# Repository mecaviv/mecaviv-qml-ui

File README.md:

# Mecaviv QML UI - Monorepo

Système complet de contrôle et visualisation pour sirènes musicales mécaniques, développé en Qt6/QML et Node.js.

## 🎯 Vue d'ensemble

Ce monorepo regroupe 4 applications interconnectées pour le contrôle, la visualisation et le monitoring de 7 sirènes musicales mécaniques. L'ensemble forme un système hiérarchique où chaque composant a un rôle spécifique dans la chaîne de contrôle et de monitoring.

## 🏗️ Architecture Globale

```
┌─────────────────────────────────────────────────────────────────┐
│                        SirenConsole                             │
│              Console de Contrôle (Priorité Max)                 │
│         Gestion de 7 pupitres - Port 8001 - WebSocket          │
└────────────────────────┬────────────────────────────────────────┘
                         │
                         │ WebSocket (contrôle + monitoring)
                         ▼
┌─────────────────────────────────────────────────────────────────┐
│                     SirenePupitre (×7)                          │
│         Visualiseurs Musicaux (Interface Locale)                │
│      Portée 3D + Contrôleurs - Port 8000 - WebSocket           │
└────────────────────────┬────────────────────────────────────────┘
                         │
                         │ UDP/WebSocket (données musicales)
                         ▼
┌─────────────────────────────────────────────────────────────────┐
│                        PureData                                 │
│              Hub de Routage MIDI + Communication                │
│        Reçoit : MIDI (Reaper, Sirénium) + UDP (Pupitres)       │
└────────────────────────┬────────────────────────────────────────┘
                         │
                         │ MIDI (contrôle physique)
                         ▼
┌─────────────────────────────────────────────────────────────────┐
│                   Sirènes Physiques (×7)                        │
│              Instruments Mécaniques + VST Virtuels              │
│                   UDP → sirenRouter (monitoring)                │
└─────────────────────────┬───────────────────────────────────────┘
                          │
                          │ UDP (monitoring passif)
                          ▼
┌─────────────────────────────────────────────────────────────────┐
│                       sirenRouter                               │
│            Service de Monitoring Centralisé                     │
│      REST API (8002) + WebSocket (8003) + UDP (8004)           │
└─────────────────────────────────────────────────────────────────┘
         │
         │ WebSocket (état temps réel)
         ▼
┌─────────────────────────────────────────────────────────────────┐
│                    pedalierSirenium                             │
│         Interface Pédalier 3D (8 pédales × 7 sirènes)          │
│     Port 8010 - WebSocket - Gestion Scènes + Presets          │
└─────────────────────────────────────────────────────────────────┘
```

## 📦 Projets Inclus

### 1. [SirenePupitre](./SirenePupitre/) - Visualiseur Musical 🎵

**Interface locale** pour visualiser en temps réel les données musicales d'une sirène.

**Fonctionnalités** :
- Portée musicale 3D avec clé de sol/fa
- Afficheurs LED 3D (Hz, RPM, note)
- Indicateurs de contrôleurs (volant, joystick, faders)
- Panneau admin (configuration, visibilité, couleurs)
- Mode console (contrôle à distance par SirenConsole)

**Technologies** : Qt 6, QML, Qt Quick 3D, WebAssembly  
**Port** : 8000  
**README** : [SirenePupitre/README.md](./SirenePupitre/README.md)

### 2. [SirenConsole](./SirenConsole/) - Console de Contrôle 🎛️

**Console centrale** pour gérer jusqu'à 7 instances de SirenePupitre.

**Fonctionnalités** :
- Vue d'ensemble de 7 pupitres
- Configuration centralisée (sirènes, contrôleurs, courbes)
- Assignation exclusive des sirènes (1 sirène = 1 pupitre)
- Mode "All" (configuration simultanée de tous les pupitres)
- Gestion de presets avec API REST
- Monitoring en temps réel

**Technologies** : Qt 6, QML, WebAssembly, Node.js  
**Port** : 8001  
**README** : [SirenConsole/README.md](./SirenConsole/README.md)

### 3. [pedalierSirenium](./pedalierSirenium/) - Interface Pédalier 3D 🎮

**Interface de contrôle 3D** pour 8 pédales contrôlant 7 sirènes.

**Fonctionnalités** :
- Vue 3D de 7 sirènes avec animations
- Matrice de configuration : 8 pédales × 7 sirènes × 8 contrôleurs = 448 paramètres
- Gestion de presets (sauvegarde/chargement)
- Gestion de scènes (64 scènes sur 8 pages)
- Contrôle de boucles (recording, playing, stopped, cleared)
- Monitoring MIDI temps réel avec portées musicales
- Debug panel avec 11 catégories de logs

**Technologies** : Qt 6, QML, Qt Quick 3D, WebAssembly, PureData  
**Port** : 8010  
**README** : [pedalierSirenium/README.md](./pedalierSirenium/README.md)

### 4. [sirenRouter](./sirenRouter/) - Service de Monitoring 📊

**Service de monitoring centralisé** pour observer l'état des sirènes.

**Fonctionnalités** :
- Monitoring passif des sirènes via UDP
- API REST pour consultation de l'état
- WebSocket pour notifications temps réel
- Dashboard web de monitoring
- Historique et logs des activités

**Technologies** : `SirenRouter.fsproj` (HTTP 8002). Le module Node de ce dossier est `src/api/control.js`.  
**Ports prévus** : 8002 (API REST), 8003 (WebSocket), 8004 (UDP)  
**README** : [sirenRouter/README.md](./sirenRouter/README.md)

## Serveurs .NET

La configuration CMake exécute `dotnet tool restore` et, si `dotnet paket` répond, `dotnet paket restore`. Depuis cette racine :

```bash
dotnet watch --non-interactive --project <projet>
dotnet run --project <projet>
```

| Projet | Rôle |
|---|---|
| `SirenManager/backend/fsharpwebserver` | API SSH / UDP, ports 8005 et 8006 |
| `SirenManager/webfiles` | fichiers WASM, port 8081 |
| `SirenePupitre/webfiles` | fichiers WASM, port 8000. L'API MIDI est `server.js` |
| `SirenConsole/webfiles` | fichiers WASM, port 8001. Presets, MIDI et `/ws` sont `server.js` |
| `pedalierSirenium/webfiles` | fichiers WASM, port 8010. Journaux, `/api` et le WebSocket 10000 sont `server.js` |
| `sirenRouter` | HTTP 8002 |

## 🚀 Installation Rapide

### Prérequis

- **Qt 6.10+** avec support WebAssembly
- **Node.js 18+** et npm
- **.NET SDK 10** (`dotnet watch`, `dotnet run`)
- **CMake 3.19+** (système de build multiplateforme)
- **Ninja** (générateur de build recommandé)
- **Google Chrome** (pour le développement web)

### Installation des Outils

```bash
# macOS
brew install cmake ninja node

# Linux
sudo apt-get install cmake ninja-build nodejs npm

# Windows
# Installer CMake: https://cmake.org/download/
# Installer Node.js: https://nodejs.org/
```

### Installation Qt WebAssembly

Télécharger Qt depuis [qt.io/download](https://www.qt.io/download) et installer les modules :
- Qt 6.10.0 (ou plus récent)
- Qt for WebAssembly (wasm_singlethread)

### Configuration des Chemins Qt

**⚠️ Important** : Le projet utilise des variables d'environnement pour les chemins Qt.

#### Configuration Rapide

```bash
# macOS / Linux
./scripts/setup-env.sh

# Windows (PowerShell)
.\scripts\setup-env.ps1
```

Le script détecte automatiquement votre système et configure les chemins Qt.

#### Configuration Manuelle

```bash
# macOS / Linux - Ajouter à ~/.zshrc ou ~/.bashrc
export QT_DIR="$HOME/Qt/6.10.0/macos"  # ou gcc_64 pour Linux
export QT_WASM_DIR="$HOME/Qt/6.10.0/wasm_singlethread"

# Windows - PowerShell ou Variables Système
$env:QT_DIR = "C:\Qt\6.10.0\msvc2019_64"
$env:QT_WASM_DIR = "C:\Qt\6.10.0\wasm_singlethread"
```

**📖 Guide détaillé** : Voir [CONFIG.md](./CONFIG.md) pour la configuration complète.

### Build de tous les projets

#### Méthode 1 : CMake (Recommandé - Multiplateforme)

```bash
# Cloner le dépôt
git clone https://github.com/mecaviv/mecaviv-qml-ui.git
cd mecaviv-qml-ui

# Configurer les variables Qt (voir CONFIG.md)
export QT_DIR="$HOME/Qt/6.10.0/macos"
export QT_WASM_DIR="$HOME/Qt/6.10.0/wasm_singlethread"

# Configuration
cmake --preset=default        # Desktop natif
# ou
cmake --preset=wasm          # WebAssembly

# Build (5-10 minutes)
cmake --build build --parallel
```

#### Méthode 2 : Scripts Bash (macOS/Linux uniquement)

```bash
# Build tous les projets
./scripts/build-all.sh
```

### Lancer un projet en mode développement

```bash
# SirenePupitre
./scripts/dev.sh sirenepupitre

# SirenConsole (serveur F#, par franz)
franz build qml-ui -p wasm -t console   # WebAssembly build, copied into SirenConsole/webfiles
franz run console-server                # F# server, https://localhost:8001 (franz stop console-server)

# pedalierSirenium
./scripts/dev.sh pedalier

# sirenRouter
./scripts/dev.sh router
```

## 📜 Build System

### CMake (Recommandé - Multiplateforme)

```bash
# Configuration
cmake --preset=default        # Desktop Debug
cmake --preset=release        # Desktop Release
cmake --preset=wasm          # WebAssembly

# Build
cmake --build build          # Build tout
cmake --build build --target appSirenePupitre  # Build un projet
cmake --build build --parallel  # Build parallèle

# Helper scripts
./scripts/configure.sh default   # macOS/Linux
.\scripts\configure.ps1 default    # Windows (PowerShell)
```

### Scripts Bash (Legacy - Unix uniquement)

```bash
./scripts/build-all.sh         # Build tous les projets
./scripts/build-project.sh <project>  # Build un projet spécifique
./scripts/dev.sh <project>     # Mode développement
./scripts/clean-all.sh         # Nettoyage complet
```

**Documentation complète** : 
- [docs/BUILD.md](./docs/BUILD.md) - Guide de build détaillé
- [scripts/README.md](./scripts/README.md) - Documentation des scripts

## 📡 Communication entre Applications

### Protocoles Utilisés

- **WebSocket** : Communication temps réel entre Console ↔ Pupitres ↔ PureData
- **UDP** : Données musicales (Pupitres → PureData, Sirènes → Router)
- **MIDI** : Contrôle physique des sirènes (PureData → Sirènes)
- **REST API** : Consultation de l'état (sirenRouter)

### Ports Utilisés

| Application | Protocol | Port(s) | Description |
|-------------|----------|---------|-------------|
| SirenePupitre | HTTP + WebSocket | 8000 | Interface web + communication |
| SirenConsole | HTTP + WebSocket | 8001 | Interface web + contrôle pupitres |
| sirenRouter | REST + WebSocket + UDP | 8002-8004 | API, notifications, monitoring |
| pedalierSirenium | HTTP + WebSocket | 8010 | Interface web + communication |
| PureData | WebSocket | 10000-10001 | Hub central de routage |

### Messages WebSocket

Voir la documentation détaillée : [docs/COMMUNICATION.md](./docs/COMMUNICATION.md)

## 📚 Documentation

- **[ARCHITECTURE.md](./docs/ARCHITECTURE.md)** : Architecture détaillée du système
- **[BUILD.md](./docs/BUILD.md)** : Guide de build complet et troubleshooting
- **[COMMUNICATION.md](./docs/COMMUNICATION.md)** : Protocoles de communication
- **[COMPOSESIREN_ARCHITECTURE.md](./docs/COMPOSESIREN_ARCHITECTURE.md)** : Architecture ComposeSiren et flux MIDI
- **[TODO.md](./TODO.md)** : Roadmap et tâches à venir

### Documentation par Projet

- [SirenePupitre/README.md](./SirenePupitre/README.md)
- [SirenConsole/README.md](./SirenConsole/README.md)
- [pedalierSirenium/README.md](./pedalierSirenium/README.md)
- [sirenRouter/README.md](./sirenRouter/README.md)

## 🎯 Use Cases Typiques

### Concert/Performance

1. **Démarrer sirenRouter** pour le monitoring
2. **Démarrer PureData** comme hub central
3. **Démarrer 7 instances de SirenePupitre** (une par sirène)
4. **Démarrer SirenConsole** pour le contrôle global
5. **Utiliser pedalierSirenium** pour les effets live

### Développement/Debug

1. **Démarrer un seul pupitre** : `./scripts/dev.sh sirenepupitre`
2. **Tester les communications** avec le debug panel
3. **Modifier le code QML** et recharger
4. **Consulter les logs** : `tail -f /tmp/sirenepupitre_server.log`

### Configuration des Sirènes

1. **Ouvrir SirenConsole**
2. **Onglet Configuration** → Sélectionner un pupitre
3. **Assigner les sirènes** (assignation exclusive)
4. **Configurer l'ambitus, la transposition, les contrôleurs**
5. **Sauvegarder en preset** pour réutiliser

## 🔧 Dépannage

### Port déjà utilisé

```bash
# Utiliser le script de nettoyage
./scripts/clean-all.sh

# Ou tuer manuellement
lsof -ti:8000 | xargs kill -9
```

### Build échoue

```bash
# Nettoyer et rebuilder
./scripts/clean-all.sh
./scripts/build-project.sh <project>
```

### Qt WebAssembly introuvable

Vérifier le chemin dans `scripts/build-project.sh` :
```bash
QT_CMAKE="$HOME/Qt/6.10.0/wasm_singlethread/bin/qt-cmake"
```

### Plus de dépannage

Voir [docs/BUILD.md](./docs/BUILD.md) pour le guide complet.

## 🗂️ Structure du Monorepo

```
mecaviv-qml-ui/
├── README.md                    # Ce fichier
├── TODO.md                      # Roadmap globale
├── .gitignore                   # Fichiers à ignorer
├── docs/                        # Documentation globale
│   ├── ARCHITECTURE.md
│   ├── BUILD.md
│   └── COMMUNICATION.md
├── scripts/                     # Scripts centralisés
│   ├── build-all.sh
│   ├── build-project.sh
│   ├── dev.sh
│   ├── clean-all.sh
│   └── README.md
├── SirenePupitre/              # Visualiseur musical
│   ├── README.md
│   ├── QML/
│   └── webfiles/
├── SirenConsole/               # Console de contrôle
│   ├── README.md
│   ├── QML/
│   └── webfiles/
├── pedalierSirenium/          # Interface pédalier 3D
│   ├── README.md
│   ├── QtFiles/
│   └── webfiles/
└── sirenRouter/                # Service monitoring
    ├── README.md
    └── src/
```

## 🤝 Contribution

Ce projet est développé par **Mécanique Vivante** pour le contrôle de sirènes musicales mécaniques.

### Workflow Git

```bash
# Travailler sur une branche
git checkout -b feature/ma-fonctionnalite

# Commiter les changements
git add .
git commit -m "Description de la fonctionnalité"

# Pousser vers le remote
git push origin feature/ma-fonctionnalite
```

## 📄 Licence

Ce projet est développé dans le cadre du projet Mécanique Vivante.

## 🆘 Support

Pour toute question :
1. Consulter la [documentation](./docs/)
2. Vérifier les [README des projets](#-projets-inclus)
3. Consulter le [TODO.md](./TODO.md) pour les fonctionnalités en cours

## 🔄 TODO - Restructuration Planifiée

### Dossier partagé `shared/` (En cours)

Pour éviter la duplication de code entre projets, création d'un dossier `shared/` à la racine du monorepo.

#### Structure prévue

```
mecaviv-qml-ui/
├── shared/
│   └── qml/
│       ├── common/              # Composants QML partagés
│       │   ├── DigitLED3D.qml
│       │   ├── LEDText3D.qml
│       │   ├── LEDSegment.qml
│       │   ├── Knob.qml
│       │   ├── Knob3D.qml
│       │   └── MusicUtils.qml
│       └── fonts/                # Polices musicales partagées
│           ├── MusiSync.ttf
│           └── NotoMusic-Regular.ttf
├── SirenePupitre/
│   └── QML/
│       └── utils/               # Composants spécifiques au pupitre
│           ├── meshes/          # Modèles 3D (reste local)
│           ├── Clef3D.qml
│           ├── Clef2D.qml
│           ├── Ring3D.qml
│           └── ColorPicker.qml
└── pedalierSirenium/
    └── QtFiles/qml/
        └── utils/               # Composants spécifiques pédalier
            └── VirtualKeyboard.qml
```

#### Composants à déplacer vers `shared/qml/common/`

**Actuellement dupliqués** entre SirenePupitre et pedalierSirenium :
- [X] `DigitLED3D.qml` - Afficheur 7 segments 3D
- [X] `LEDText3D.qml` - Texte LED 3D
- [X] `LEDSegment.qml` - Segment LED individuel
- [X] `Knob.qml` - Bouton rotatif 2D
- [X] `Knob3D.qml` - Bouton rotatif 3D
- [X] `MusicUtils.qml` - Utilitaires de calculs musicaux

#### Ressources à déplacer vers `shared/qml/fonts/`

**Polices musicales** utilisées par plusieurs projets :
- [X] `MusiSync.ttf` - Symboles musicaux de base
- [X] `NotoMusic-Regular.ttf` - Police Noto Music (SMuFL)

#### Composants à garder locaux

**Spécifiques à chaque projet** :
- `meshes/` - Modèles 3D (spécifiques par projet, build complexe)
- `Clef3D.qml`, `Clef2D.qml` - Clés musicales (SirenePupitre)
- `Ring3D.qml`, `ColorPicker.qml` - Utilitaires UI (SirenePupitre)
- `VirtualKeyboard.qml` - Clavier virtuel (pedalierSirenium)

#### Modifications nécessaires

**Scripts à adapter** :
- [ ] `SirenePupitre/scripts/build.sh` - Copier fonts depuis shared/
- [ ] `pedalierSirenium/scripts/build.sh` - Copier fonts depuis shared/
- [ ] `scripts/convert-clefs.sh` - Chemins meshes/ (reste local)

**Fichiers de ressources** :
- [ ] `data.qrc` - Références vers `../shared/qml/`
- [ ] `CMakeLists.txt` - Inclusion des chemins shared/

**Imports QML** (environ 20+ fichiers) :
- [ ] Mettre à jour les imports `import "../utils"` → `import "../../../shared/qml/common"`
- [ ] Mettre à jour les imports fonts `qrc:/QML/fonts/` → `qrc:/shared/qml/fonts/`

### Bibliothèque MIDI externe (À faire)

#### Déplacer `midifiles/` vers un repository séparé

**Raison** : La bibliothèque MIDI (40+ fichiers, compositions musicales) mérite son propre repository pour :
- Gestion de versions indépendante
- Partage avec d'autres projets
- Historique Git dédié aux compositions

**Structure prévue** :
```
mecaviv-midi-library/           # Nouveau repository
├── README.md
├── louette/                    # Compositions de Louette (40+ fichiers)
├── patwave/                    # Compositions de Patwave (4 fichiers)
├── covers/                     # Adaptations et reprises
└── presets/                    # Configurations de presets
```

**Intégration** :
- [ ] Créer repository `mecaviv-midi-library`
- [ ] Déplacer `SirenePupitre/midifiles/` vers le nouveau repo
- [ ] Ajouter en submodule Git : `git submodule add <url> shared/midi`
- [ ] Mettre à jour les scripts pour référencer `shared/midi/`

---

**Mécanique Vivante** - Système de Contrôle de Sirènes Musicales 🎵

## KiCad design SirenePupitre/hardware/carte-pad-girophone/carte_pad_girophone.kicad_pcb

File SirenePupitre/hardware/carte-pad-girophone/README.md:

# Carte Pad Girophone

Projet KiCad 9 reconstruit à partir de `Carte_Pad_Girophone.pdf` (maquette de câblage manuscrite,
Septembre 2026). Fichiers : `carte_pad_girophone.kicad_pro/.kicad_sch/.kicad_pcb`.

Fabrication : plaque nue chez JLCPCB. **Composants et connecteurs montés à la main**, pas
d'assemblage JLC — pas de BOM/CPL à fournir, seulement les Gerbers + le fichier de perçage.

## Carte

- 51 mm × 72 mm, 4 trous de fixation Ø2mm non métallisés, entraxes 45×66mm (inset 3mm).
- U1/U2 : 2× embase femelle 1×7 (2.54mm) pour un Seeed XIAO ESP32-S3 monté sur pins (amovible).
  Écartement des deux rangées : **15.24mm**, vérifié contre l'empreinte officielle Seeed
  (`XIAO-ESP32-S3-DIP.kicad_mod`, dans `New_XIAO_Series_Footprints.zip` du wiki Seeed).
- J1 MTA6 (Joystick), J2 MTA5 (XLR), J3 MTA3 (Slider), J4 MTA5 (PAD), J5 MTA4 (passthrough USB) :
  tous en pas 2.54mm, footprint générique (`Connector_PinHeader_2.54mm`) — remplacer par
  l'empreinte exacte si la référence Molex/TE réelle diffère en pas ou en détrompage.
- R1/R2 : pull-down des pads velostat, **12k**. R3/R4 : résistances série des LED, **47Ω**
  (valeurs confirmées par Patrice — le croquis ne donnait qu'une lecture approximative du
  code couleur, 10k/1k, qui était fausse).

## Brochage du XIAO — vérifié contre la config NVS de référence

Le croquis d'origine numérote les pins localement (1-7 par rangée) sans donner les vrais noms
Seeed. La correspondance ci-dessous croise trois sources indépendantes : le schéma officiel
Seeed (`XIAO-ESP32-S3-SMD`, pins 1-14), l'empreinte DIP officielle (position physique de chaque
pin), et surtout `SirenePupitre/firmware/nvs/gyrophone-pad.csv` + `NiDMI/src/utils/PinMapper.cpp`
— la config NVS réellement utilisée par le firmware NiDMI sur la carte de référence. Les deux
concordent pin par pin (voir tableau), ce qui confirme le sens de lecture retenu.

| Position socket | U1 | Fonction (réf. NVS) | U2 | Fonction (réf. NVS) |
|---|---|---|---|---|
| 1 | D7 / GPIO44 | → R4 → LED2 (J4.2) | *(NC)* | — |
| 2 | D8 / GPIO7 | joystick Z (J1.6) | D5 / GPIO6 | → R3 → LED1 (J4.1) |
| 3 | D9 / GPIO8 | joystick X (J1.4) | D4 / GPIO5 | pad2 / velostat (J4.4, via R1 pull-down) |
| 4 | D10 / GPIO9 | **joystick, 3e axe (J1.2)** — corrigé, n'est plus sur le bus 3.3V | D3 / GPIO4 | pad1 / velostat (J4.3, via R2 pull-down) |
| 5 | 3V3_OUT | fournit le 3.3V au bus commun | *(NC)* | libérée à nouveau — reste candidate pour un futur bouton |
| 6 | GND | GND | D1 / GPIO2 | slider (J3.3) |
| 7 | *(NC)* | — | D0 / GPIO1 | signal XLR (J2.5) |

Concordance avec `gyrophone-pad.csv` : A1→slider ✓, A3→pad1 ✓, A4→pad2 ✓, D5→LED1 ✓, D7→LED2 ✓.
Ces cinq correspondances confirmaient indépendamment le sens de lecture (inversé une fois en
cours de route — voir historique ci-dessous), donc la confiance dans le reste du tableau est
haute.

**Correction du 2026-09-08 (revenue en arrière, puis réutilisée)** : j'avais un temps câblé
A2/GPIO3/D2 (position 5 de U2) sur le bouton du joystick (J1.3), en me basant sur la convention
NiDMI du pupitre (`D2.json` : role=`button`). Patrice a signalé que **le 3.3V est commun à tous
les potards (joystick, slider) ET aux pads** — J1.3 est donc l'alimentation 3.3V du joystick, pas
un bouton. J1.3 est retourné sur le bus 3.3V commun.

**Deuxième correction, même jour** : en vérifiant le câblage des potentiomètres (GND/3.3V/sonde
pour chacun), la sonde de l'axe Y du joystick (J1.2) s'est révélée être sur le **même fil que
PAD1** (net alors nommé `N_PAD3_JOYY`) — avec le pull-down 12k de R2 dessus. Patrice a confirmé
qu'il y a bien 4 résistances distinctes (2×47Ω LED, 2×12k pad), donc pad1 et joystick Y doivent
lire sur deux broches ADC séparées, pas partager la même. Fixé en déplaçant J1.2 sur **A2/GPIO3
(U2 position 5)**, qui était justement la broche restée inutilisée — pad1 (J4.3/U2.4/R2) garde
son fil propre, renommé `N_PAD1`.

**Point résolu (2026-09-08)** : U1 position 4 (D10/GPIO9) était par erreur sur le même bus que le
3.3V — erreur de lecture du croquis d'origine de ma part (un point que j'avais pris pour une
connexion au bus 3.3V était en fait le fil du 3e axe du joystick). Trouvé en comparant le câblage
avec la config NVS de référence : le joystick 3 axes y occupe trois broches **consécutives**
(GPIO7-8-9, A8 + additionalPins joyYPin/joyZPin), donc GPIO9 ne peut pas aussi porter du 3.3V.
Corrigé : J1.2 (le 3e fil du joystick) va maintenant sur U1.4/GPIO9 ; U1.5/3V3_OUT alimente
uniquement le bus commun (J1.3, J3.1). U2 position 5 (A2/GPIO3) est repassée en NC — elle reste
la candidate la plus probable pour un futur bouton, si le connecteur qui le porte est identifié.

Le lien entre le bus 3.3V et les **pads** (velostat) mentionné par Patrice n'est pour l'instant
pas visible sur J4 (5 broches déjà toutes attribuées : 2 LED + 2 pad signal + GND) — probablement
câblé en dehors de cette carte (jonction dans le faisceau), à confirmer.

## Historique des corrections de brochage (2026-09-08)

1. Écartement U1/U2 : 17.78mm → 15.24mm (mesuré sur l'empreinte officielle Seeed).
2. Ordre des pins dans chaque socket inversé (1↔7, 2↔6, 3↔5) — confirmé par Patrice après
   comparaison avec le module physique.
3. ~~Position U2.5 (D2/GPIO3/A2) connectée au bouton du joystick (J1.3)~~ — **revenu en arrière** :
   le 3.3V est commun à tous les potards ET aux pads (confirmé par Patrice), donc J1.3 reste sur
   le bus 3.3V et U2.5 est repassée en NC, comme dans le croquis d'origine.
4. Placement réaligné sur les coordonnées mesurées du PDF d'origine (USBC et XIAO à la même
   hauteur ; R1/R2 sous l'USB comme sur le croquis ; R3/R4 juste à droite du XIAO plutôt que
   plaquées au bord de la carte).
5. Valeurs R1-R4 corrigées (12k / 47Ω) et footprint résistance passé en axial horizontal (couché,
   corps+bagues visibles) — la version verticale "debout" rendait comme un simple strap cuivre.

## Netlist complète

| Net | Broches |
|---|---|
| GND | J1.1, J1.5, J2.1, J3.2, J4.5, J5.1, U1.6, R1.1, R2.1 |
| N_3V3_TO_SLIDER_D10 | J1.3, J3.1, U1.5 *(3.3V commun aux potards)* |
| N_PAD1 | U2.4 (pad1), J4.3, R2.2 |
| N_JOYY | J1.2, U1.4 (D10/GPIO9, 3e axe joystick) — déplacé du bus 3.3V le 2026-09-08 |
| N_PAD4 | U2.3 (pad2), J4.4, R1.2 |
| N_JOYX | J1.4, U1.3 |
| N_JOYZ | J1.6, U1.2 |
| N_XLR5 | J2.5, U2.7 |
| N_SLIDER3 | J3.3, U2.6 |
| N_R3A / N_R3B | U2.2 (LED1) —R3— J4.1 |
| N_R4A / N_R4B | U1.1 (LED2) —R4— J4.2 |
| USB_DM / USB_DP / USB_VBUS | J2.2-4 ↔ J5.2-4 (XLR relaie l'USB de J5) |

## Points laissés en suspens

- **ERC** : 2 fausses alertes ("pin non connectée" sur J1.6 et J5.4) persistent alors que le rendu
  PDF confirme que le label est bien au bon endroit — ça ressemble à un bug de `kicad-cli` 9.0.7
  sur les fichiers écrits à la main plutôt qu'un vrai défaut. Ignorable, ou se résout tout seul en
  rouvrant/sauvant une fois dans l'éditeur de schéma.
- Le bus GND9/3V3 sur U1 positions 4-5 (voir plus haut) — à trancher avant de souder.

## Ce qu'il reste à faire avant d'envoyer à JLCPCB

1. Ouvrir `carte_pad_girophone.kicad_pcb` dans PCB Editor.
2. **Router les pistes signal** (ratsnest visible, ~14 nets, tous P2.54mm à faible densité —
   quelques minutes avec le routeur interactif). Non fait ici : un routage à l'aveugle sans retour
   visuel aurait été trop risqué (court-circuit invisible sur une vraie commande de PCB).
3. **Remplir le plan de masse GND** (zone déjà posée sur B.Cu, mais non remplie — `ZONE_FILLER`
   plante en scripting headless sans affichage). Édition > Remplir toutes les zones (`B`).
4. Lancer le DRC (`Inspecter > Vérification des règles de conception`), corriger si besoin.
5. Trancher le point non résolu (D10/3V3 sur U1).
6. Fichiers > Fabrication > Gerbers (+ fichier de perçage) → zip → JLCPCB.

## Fichiers annexes

- `preview.pdf` : rendu du schéma (texte tassé sur chaque connecteur — cosmétique seulement,
  à réarranger si besoin dans l'éditeur).
- `pcb_render_top.png` : rendu 3D du placement des empreintes.

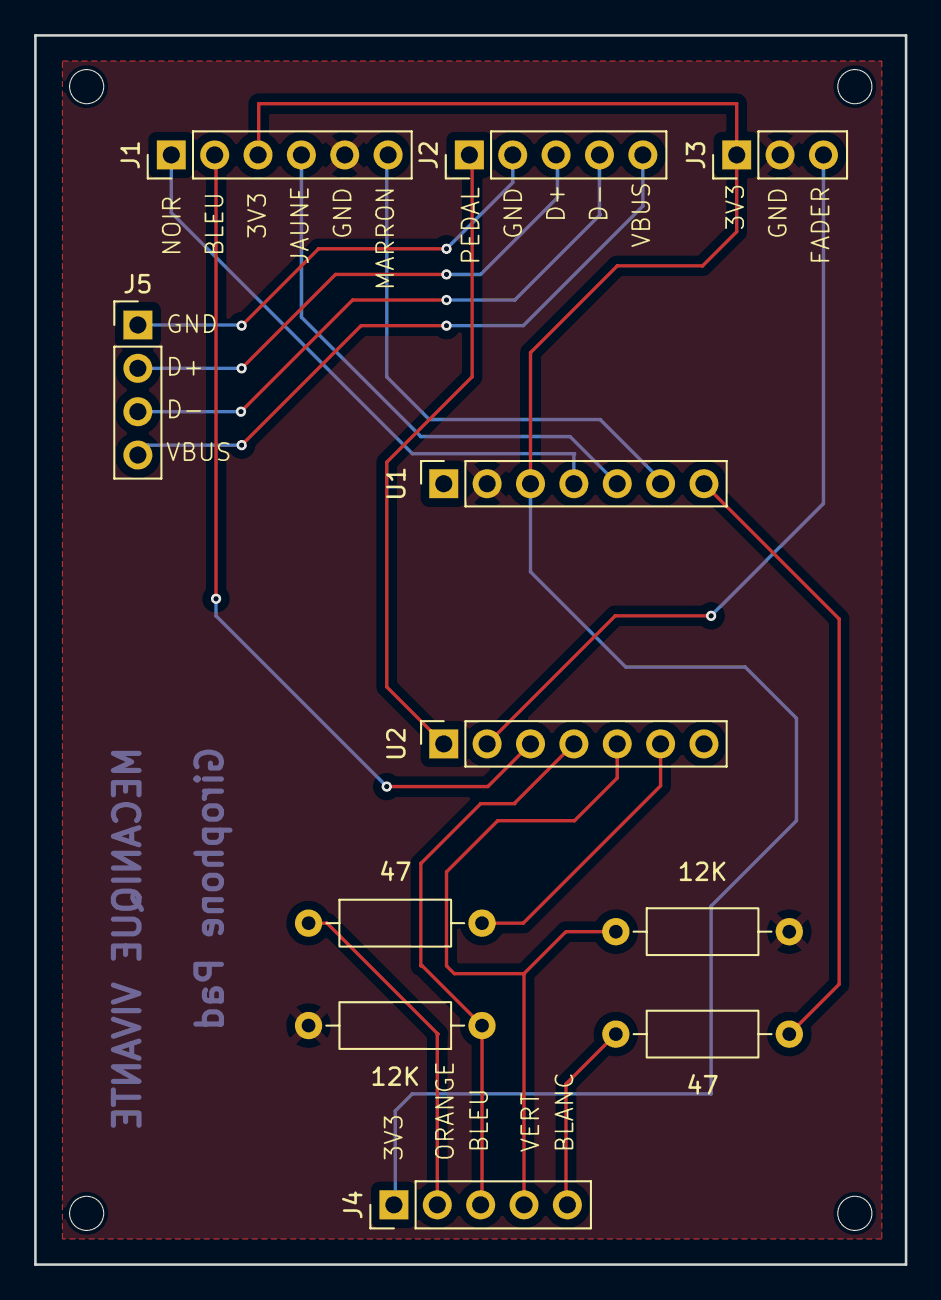
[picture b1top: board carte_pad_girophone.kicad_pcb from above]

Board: 2 copper layers, 51.0 x 72.0 mm, 11 parts (0 on the bottom side), 18 nets.

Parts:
12K, 12K#2: 12k; R_Axial_DIN0207_L6.3mm_D2.5mm_P10.16mm_Horizontal
47, 47#2: 47R; R_Axial_DIN0207_L6.3mm_D2.5mm_P10.16mm_Horizontal
J1: MTA6_Joystick; PinHeader_1x06_P2.54mm_Vertical
J2: MTA5_XLR; PinHeader_1x05_P2.54mm_Vertical
J3: MTA3_Slider; PinHeader_1x03_P2.54mm_Vertical
J4: MTA5_PAD; PinHeader_1x05_P2.54mm_Vertical
J5: MTA4_USB_passthrough; PinHeader_1x04_P2.54mm_Vertical
U1: XIAO_ESP32S3_socket_TOP; PinSocket_1x07_P2.54mm_Vertical
U2: XIAO_ESP32S3_socket_LEFT; PinSocket_1x07_P2.54mm_Vertical

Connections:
+3.3V: J1.3, J3.1, J4.1, U1.3
GND: 12K.2, 12K#2.2, J1.5, J3.2, U1.2
unnamed: J1.1, U1.4
unnamed: J1.2, U2.3
unnamed: J1.4, U1.5
unnamed: J1.6, U1.6
unnamed: J2.1, U2.1
unnamed: J2.2, J5.1
unnamed: J2.3, J5.2
unnamed: J2.4, J5.3
unnamed: J2.5, J5.4
unnamed: J3.3, U2.2
unnamed: 47.1, J4.2
unnamed: 12K#2.1, J4.3, U2.4
unnamed: 12K.1, J4.4, U2.5
unnamed: 47#2.1, J4.5
unnamed: 47#2.2, U1.7
unnamed: 47.2, U2.6
